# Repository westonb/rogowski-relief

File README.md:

# rogowski-relief
## An open source rogowski coil based current probe

This project is a rogowski coil based current probe designed to measure high frequency AC currents in tight spaces.
The sensing coil is optimized to be small enough to fit between the leads of a TO-220 transistor and can be slipped around the leads of many through hole power components for non-intrusive current measurements. 
The project consists of the rogowski coil and the integrator/amplifier which conditions the signal from the rogowski coil and provides an output voltage proportional to the current flowing in a conductor encircled by the rogowski coil. 

## Operation
The sensing coil is open ended, with the free end held in place by a captive O-ring.
The enables the coil to be placed around a wire without breaking the circuit.
The amplifier provides a 0.1V/A output through a SMA connector and is designed to drive a 1M oscilloscope input through a coaxial cable. 
The amplifier is powered through a USB-B connector and draws less than 2W. 

## Specifications 

### Typical Electrical Performance

- **Bandwidth**: 800 Hz - 25 MHz
- **Sensitivity**: 0.1 Volts/Amp
- **Max Current**: +/- 30 A
- **Noise**: 6 mA RMS
- **Slew Rate**: 1 A/ns 

### Coil
- **OD**: < 1.7mm
- **Length**: 70mm

## Project Status
The current probe meets the original design goals and is suitable for general purpose lab use.
The most recently fabricated version of the integrator had some issues with interference from wireless signals (WiFi and LTE).
The PCB files in the latest commit have layout changes to fit the circuitry under a metal shielding can, which should largely remedy the issue.
There are only minor electrical revisions in the updated version, but it remains untested.

## Project Files

LTSpice simulation files for the time domain and frequency domain as well as noise simulation of the system are in the [sim](sim/) directory.
PCB design files and schematics are in the [PCB](pcb/) directory.
STL files of for the rogowski coil, mechanical BOM, and build instructions are in the [mech](mech/) directory.
Schematic of the integrator provided below for convenience. 

## Operating Principles 

### Rogowski Coil

|  | 
|:--:| 
| *Rogowski Coil Drawing. Source: [Wikipedia](https://en.wikipedia.org/wiki/File:Rogowski_coil.png)* |

A rogowski coil is a toroidally wound air coil, consisting of many turns of wire wrapped around a coil form, with the start and end of the coil form joined together.
Each turn of the coil generates a voltage proportional to the change in the coupled magnetic field.
The sum of the voltage produced by all the turns is proportional to the change in the line integral of magnetic field around the path of the coil. 
As expressed by Ampere's law, the line integral of the magnetic field for any closed path is proportional to the current flowing in the enclosed area. 
Thus, the rogowski coil produces a voltage proportional to the change in current in a wire encircled by the coil with the output signal independent of the positioning of the wire. 
This allows for a flexible air-cored current sensor.
Unlike a current transformer, the rogowski coil generates a voltage proportional to the dI/dt and the signal must be integrated to produce an output proportional to current.
Additionally, as the dI/dt of a DC current is zero, the rogowski coil can not measure a DC current. 

|  | 
|:--:| 
| *Circuit Model of Rogowski Coil* |

The rogowski coil can be modeled as a mutual inductance representing the flux coupling between the encircled wire and the coil, and the physical inductance and capacitance of the coil.
The induced signal can be modeled as a current source equal to that of the current in the encircled wire that is parallel with the mutual inductance.
The inductance and capacitance of the coil limit the maximum bandwidth and are dependent on the geometry of the coil.
The winding diameter and pitch determine the characteristic impedance of the coil, which determines the ratio of inductance to capacitance.
The bandwidth of the rogowski coil is maximized when the coil is terminated with a resistance equal to the characteristic impedance.
The total values of inductance and capacitance are determined by the length of the coil, which is proportional to the number of turns.

### Integrator
This project uses an op-amp based integrator to process the signal from the rogowski coil.
As integrator gain increases at low frequencies, the noise of the integrator ultimately limits the achievable low frequency bandwidth and is one of the most important design criteria.

This design uses an non-inverting integrator, best described in the paper [High Performance Rogowski Current Transducers](https://gmw.com/wp-content/uploads/2019/01/ias_2000_pem.pdf), and a servo high-pass filter with a second op-amp, best described in [A new filter topology for analog high-pass filters](https://www.ti.com/lit/an/slyt299/slyt299.pdf) to roll off the low frequency gain.

|  | 
|:--:| 
| *Annotated schematic of Rogowski coil and integrator* |

The non-inverting integrator consists of a passive RC integrator for high frequency integration and an op-amp integrator for low frequencies.
The passive RC integrator is comprised of the termination resistor for the rogowski coil, which matches the characteristic impedance of the rogowski coil and is co-located with the rogowski coil.
This allows for the capacitance of the cable between the rogowski coil and the integrator, which would otherwise limit bandwidth, to be incorporated as part of the integrator capacitance.
The non-inverting integrator requires that the crossover frequencies of the passive RC integrator and the op-amp match, necessitating a trimmer resistor.

The servo high-pass filter reduces the gain of the integrator below the cutoff frequency instead of leveling off the gain.
This reduces the noise of the system and nulls the DC offset of the amplifier, which could otherwise limit the output signal range.

An additional op-amp is used as an output buffer to provide adjustable gain to normalize the output to a fixed V/A ratio, and provide high frequency peaking to compensate for losses in the rogowski coil.

The op-amp used for the integrator was chosen for its low noise and high bandwidth.
Changing the op-amp can drastically change the output noise.

### Power Supply
The integrator is powered through a USB-B connector.
An isolated DC/DC converter module is uses to provide bipolar outputs of +/-9V which is then regulated down to +/-6V with linear regulators.
The linear regulators reduce switching noise which could otherwise couple into the output.
The isolated DC/DC converters are a commodity component that provide a bipolar output with lower cost and complexity than could be achieved with a solution using discrete components.
Additionally, the isolated module prevents any return current from passing through the output cable, which can inject noise or cause a DC offset.

## Safety 
No safety guarantees or warranty is implied for this design.
However, some safety precautions were taken as the rogowski coil could come into contact with conductors that are at a high voltage.
A PCB trace fuse on both connections from the coil is included on the PCB layout in the hope that the traces will blow and isolate the coil if the coil arcs over.
Additionally, a gas discharge tube is included on the output to further protect a connected device if such an arc-over would occur.

No voltage rating of the rogowski coil is implied or tested
The recommended heat-shrink has a wall thickness of 8 mil and a dielectric strength of 2kV/mil.
The recommended magnetic wire is MW 35-C rated and as such has a minimum dielectric strength of 2340V.
Mechanical wear and high dv/dt signals both adversely impact the voltage rating.

## Demo
|  | 
|:--:| 
| *Probe step response. Reference (yellow) and probe output (orange)* |

|  | 
|:--:| 
| *Output Noise and FFT* |

|  | 
|:--:| 
| *Probe frequency response* |

|   | 
|:--:| 
| *Probing primary current (yellow) and output choke current (orange) of a SMPS* |

## Open Source
This work is licensed under a
[Creative Commons Attribution-ShareAlike 4.0 International License][cc-by-sa].

[![CC BY-SA 4.0][cc-by-sa-image]][cc-by-sa]

[cc-by-sa]: http://creativecommons.org/licenses/by-sa/4.0/
[cc-by-sa-image]: https://licensebuttons.net/l/by-sa/4.0/88x31.png
[cc-by-sa-shield]: https://img.shields.io/badge/License-CC%20BY--SA%204.0-lightgrey.svg

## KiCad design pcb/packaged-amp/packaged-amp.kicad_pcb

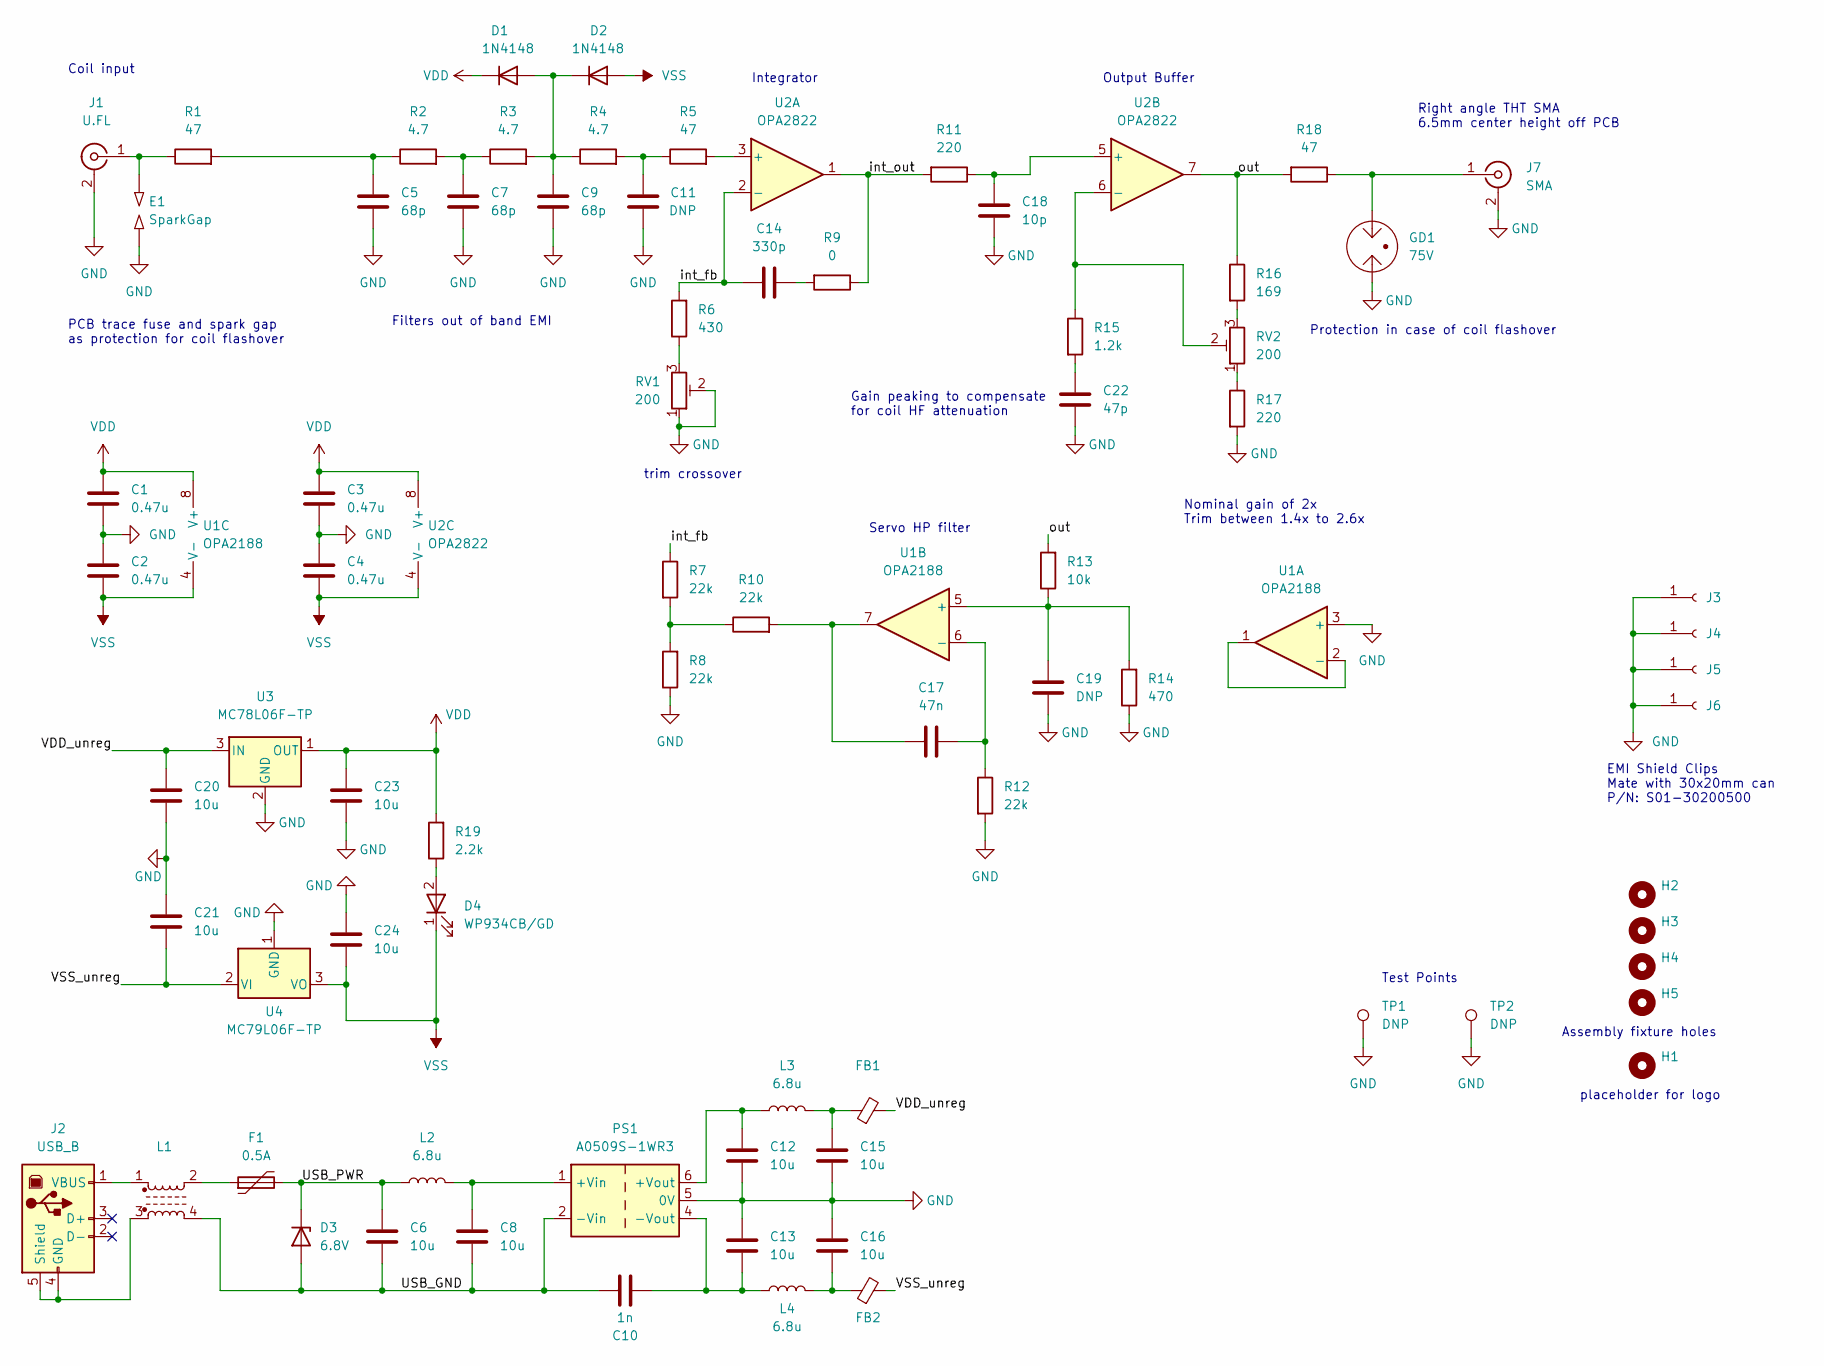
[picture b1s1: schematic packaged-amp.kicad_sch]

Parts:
C1, C2, C3, C4: 0.47u; C_0603_1608Metric; MPN CL10B474KA8NNNC; JLC_MPN C1623
C5, C7, C9: 68p; C_0603_1608Metric; MPN CL10C680JB8NNNC; JLC_MPN C28262
C6, C8, C12, C13, C15, C16, C20, C21, C23, C24: 10u; C_1206_3216Metric; MPN CL31A106KBHNNNE; JLC_MPN C13585
C10: 1n; C_1206_3216Metric; MPN 1206B102K202NT; JLC_MPN C9196
C11, C19: DNP; C_0603_1608Metric
C14: 330p; C_0603_1608Metric; MPN CL10C331JB8NNNC; JLC_MPN C1664
C17: 47n; C_1206_3216Metric; MPN GRM31M5C1H473JA01L; JLC_MPN C21812
C18: 10p; C_0603_1608Metric; MPN CL10C100JB8NNNC; JLC_MPN C1634
C22: 47p; C_0603_1608Metric; MPN CL10C470JB8NNNC; JLC_MPN C1671
D1, D2: 1N4148; D_SOD-323F; MPN 1N4148WS RRG; JLC_MPN C2128
D3: 6.8V; D_SMB; MPN P6SMB6.8CA/TR13; JLC_MPN C78395
D4: WP934CB/GD; LED-T1-RIGHT-ANGLE_4.6x4.4mm; MPN WP934CB/GD; JLC_MPN C2929607
E1: SparkGap; Spark_Gap
F1: 0.5A; Fuse_0603_1608Metric; MPN 0467.750NRHF; JLC_MPN C206991
FB1, FB2: FerriteBead_Small; L_0805_2012Metric; MPN 742792040; JLC_MPN C1015
GD1: 75V; GDT_1812; MPN 4532-075-LF; JLC_MPN C522627
H1: MountingHole; beefield_logo_small
H2, H3, H4, H5: MountingHole; JLC_TOOLING_HOLE
J1: U.FL; U.FL_Hirose_U.FL-R-SMT-1_Vertical; MPN U.FL-R-SMT-1(10); JLC_MPN C88373
J2: USB_B; USB_B_OST_USB-B1HSxx_Horizontal; MPN USB-B1HSB6; JLC_MPN C498173
J3, J4, J5, J6: Conn_01x01_Female; CLIP_ECT81800C036; MPN S1001-46R; JLC_MPN C5446941
J7: SMA; SMA_Molex_73251-2200_Horizontal; MPN RF2-49B-T-00-50-G-HDW; JLC_MPN C1509208
L1: DLW5BTM142SQ2L; L_CommonModeChoke_Murata_DLW5BTM; MPN DLW5BTM142SQ2L; JLC_MPN C91596
L2, L3, L4: 6.8u; L_1210_3225Metric; MPN NLCV32T-6R8M-EF; JLC_MPN C250230
PS1: A0509S-1WR3; Converter_DCDC_XP_POWER-IHxxxxS_THT; MPN A0509S-1WR3; JLC_MPN C131900
R1, R5: 47; R_0603_1608Metric; MPN RC0603FR-0747RL; JLC_MPN C23182
R2, R3, R4: 4.7; R_0603_1608Metric; MPN RC0603JR-074R7L; JLC_MPN C23164
R6: 430; R_0603_1608Metric; MPN RC0603FR-07430RL; JLC_MPN C23170
R7, R8, R10, R12: 22k; R_0603_1608Metric; MPN RMCF0603FG22K0; JLC_MPN C31850
R9: 0; R_0603_1608Metric; MPN ERJ-3GEY0R00V; JLC_MPN C21189
R11, R17: 220; R_0603_1608Metric; MPN RC0603FR-07220RL; JLC_MPN C22962
R13: 10k; R_0603_1608Metric; MPN RC0603FR-0710KL; JLC_MPN C25804
R14: 470; R_0603_1608Metric; MPN RC0603FR-07470RL; JLC_MPN C23179
R15: 1.2k; R_0603_1608Metric; MPN RC0603FR-071K2L; JLC_MPN C22765
R16: 169; R_0603_1608Metric; MPN RC0603FR-07169RL; JLC_MPN C22889
R18: 47; R_1206_3216Metric; JLC_MPN C17969
R19: 2.2k; R_0603_1608Metric; MPN RC0603FR-072K2L; JLC_MPN C4190
RV1, RV2: 200; Potentiometer_Bourns_3314G_Vertical; MPN 3314G-1-201E; JLC_MPN C52238
TP1, TP2: DNP; THM_MINI
U1: OPA2188; SOIC-8_3.9x4.9mm_P1.27mm; MPN OPA2188AIDR; JLC_MPN C17271
U2: OPA2822; SOIC-8_3.9x4.9mm_P1.27mm; MPN OPA2822U; JLC_MPN C2059808
U3: MC78L06F-TP; SOT-89-3; MPN MC78L06F-TP; JLC_MPN C81358
U4: MC79L06F-TP; SOT-89-3; MPN MC79L06F-TP; JLC_MPN C8619

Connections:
/USB_GND: C6.2, C8.2, C10.1, D3.2 (A), L1.4, PS1.2 (-Vin)
/USB_PWR: C6.1, D3.1 (K), F1.2, L2.1
/VDD_unreg: C20.1, FB1.2, U3.3 (IN)
/VSS_unreg: C21.2, FB2.2, U4.2 (VI)
/int_fb: C14.1, R6.2, R7.1, U2.2 (-)
/int_out: R9.1, R11.2, U2.1
/out: R13.2, R16.1, R18.2, U2.7
GND: C1.2, C2.1, C3.2, C4.1, C5.2, C7.2, C9.2, C11.1, C12.2, C13.1, C15.2, C16.1, C18.2, C19.1, C20.2, C21.1, C22.2, C23.2, C24.1, E1.1, GD1.2, J1.2 (Ext), J3.1, J4.1, J5.1, J6.1, J7.2 (Ext), PS1.5 (0V), R8.1, R12.2, R14.1, R17.2, RV1.1, RV1.2, TP1.1, TP2.1, U1.3 (+), U3.2 (GND), U4.1 (GND)
unnamed: C5.1, R1.2, R2.1
unnamed: C8.1, L2.2, PS1.1 (+Vin)
unnamed: C14.2, R9.2
unnamed: C17.1, R10.2, U1.7
unnamed: C17.2, R12.1, U1.6 (-)
unnamed: C19.2, R13.1, R14.2, U1.5 (+)
unnamed: D4.2 (A), R19.1
unnamed: E1.2, J1.1 (In), R1.1
unnamed: C15.1, FB1.1, L3.2
unnamed: C16.2, FB2.1, L4.2
unnamed: GD1.1, J7.1 (In), R18.1
unnamed: J2.1 (VBUS), L1.1
unnamed: J2.4 (GND), J2.5 (Shield), L1.3
unnamed: F1.1, L1.2
unnamed: C10.2, C13.2, L4.1, PS1.4 (-Vout)
unnamed: C12.1, L3.1, PS1.6 (+Vout)
unnamed: C7.1, R2.2, R3.1
unnamed: C9.1, D1.2 (A), D2.1 (K), R3.2, R4.1
unnamed: C11.2, R4.2, R5.1
unnamed: R6.1, RV1.3
unnamed: R7.2, R8.2, R10.1
unnamed: C18.1, R11.1, U2.5 (+)
unnamed: C22.1, R15.2
unnamed: R16.2, RV2.3
unnamed: R17.1, RV2.1
unnamed: U1.1, U1.2 (-)
unnamed: R5.2, U2.3 (+)
unnamed: R15.1, RV2.2, U2.6 (-)
VDD: C1.1, C3.1, C23.1, D1.1 (K), R19.2, U1.8 (V+), U2.8 (V+), U3.1 (OUT)
VSS: C2.2, C4.2, C24.2, D2.2 (A), D4.1 (K), U1.4 (V-), U2.4 (V-), U4.3 (VO)

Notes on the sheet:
Coil input
Gain peaking to compensate for coil HF attenuation
Servo HP filter
Integrator
PCB trace fuse and spark gap as protection for coil flashover
Test Points
Output Buffer
Protection in case of coil flashover
Right angle THT SMA 6.5mm center height off PCB
Filters out of band EMI
Assembly fixture holes
placeholder for logo
EMI Shield Clips Mate with 30x20mm can P/N: S01-30200500
Nominal gain of 2x Trim between 1.4x to 2.6x
trim crossover

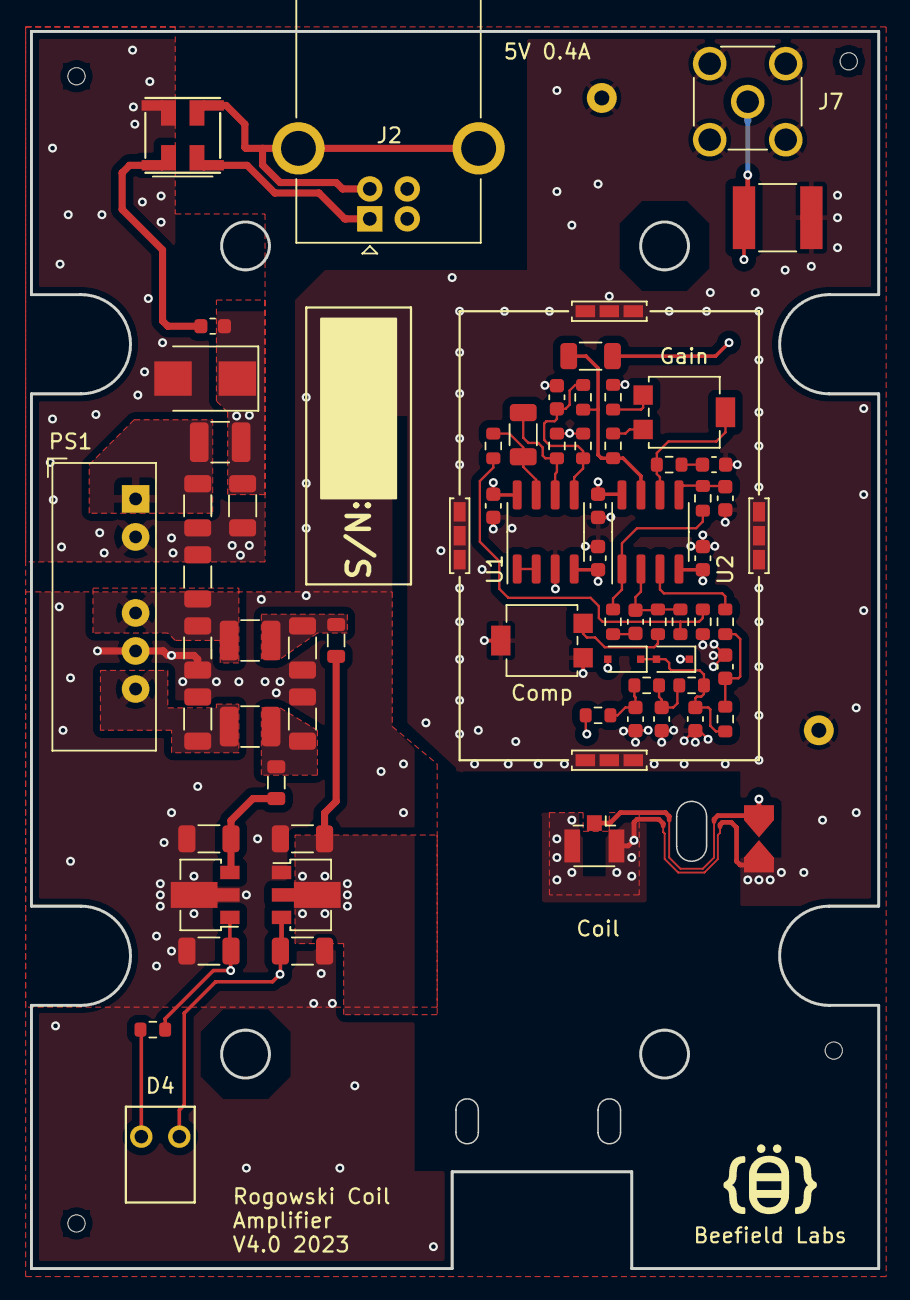
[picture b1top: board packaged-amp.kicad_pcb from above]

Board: 4 copper layers, 56.6 x 82.7 mm, 77 parts (0 on the bottom side), 38 nets.

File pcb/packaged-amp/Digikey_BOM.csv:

"Ref","Qty","Value","Footprint","Description","MPN"
"C1, C2, C3, C4, ","4","0.47u","Capacitor_SMD:C_0603_1608Metric","Unpolarized capacitor","CL10B474KA8NNNC"
"C5, C7, C9, ","3","68p","Capacitor_SMD:C_0603_1608Metric","Unpolarized capacitor","CL10C680JB8NNNC"
"C6, C8, C12, C13, C15, C16, C20, C21, C23, C24, ","10","10u","Capacitor_SMD:C_1206_3216Metric","Unpolarized capacitor","CL31A106KBHNNNE"
"C10, ","1","1n","Capacitor_SMD:C_1206_3216Metric","Unpolarized capacitor","1206B102K202NT"
"C11, C19, ","2","DNP","Capacitor_SMD:C_0603_1608Metric","Unpolarized capacitor",""
"C14, ","1","330p","Capacitor_SMD:C_0603_1608Metric","Unpolarized capacitor","CL10C331JB8NNNC"
"C17, ","1","47n","Capacitor_SMD:C_1206_3216Metric","Unpolarized capacitor","GRM31M5C1H473JA01L"
"C18, ","1","10p","Capacitor_SMD:C_0603_1608Metric","Unpolarized capacitor","CL10C100JB8NNNC"
"C22, ","1","47p","Capacitor_SMD:C_0603_1608Metric","Unpolarized capacitor","CL10C470JB8NNNC"
"D1, D2, ","2","1N4148","Diode_SMD:D_SOD-323F","Diode","1N4148WS RRG"
"D3, ","1","6.8V","Diode_SMD:D_SMB","Zener diode","P6SMB6.8CA/TR13"
"D4, ","1","WP934CB/GD","wbraun_smd:LED-T1-RIGHT-ANGLE_4.6x4.4mm","Light emitting diode","WP934CB/GD"
"E1, ","1","SparkGap","wbraun_smd:Spark_Gap","Spark gap",""
"F1, ","1","0.5A","Fuse:Fuse_0603_1608Metric","Resettable fuse, polymeric positive temperature coefficient","0467.750NRHF"
"FB1, FB2, ","2","FerriteBead_Small","Inductor_SMD:L_0805_2012Metric","Ferrite bead, small symbol","742792040"
"GD1, ","1","75V","wbraun_smd:GDT_1812","Gas Discharge Tube with 2 Pins","4532-075-LF"
"H1, ","1","MountingHole","wbraun_smd:beefield_logo_small","Mounting Hole without connection",""
"H2, H3, H4, H5, ","4","MountingHole","wbraun_smd:JLC_TOOLING_HOLE","Mounting Hole without connection",""
"J1, ","1","U.FL","Connector_Coaxial:U.FL_Hirose_U.FL-R-SMT-1_Vertical","coaxial connector (BNC, SMA, SMB, SMC, Cinch/RCA, LEMO, ...)","U.FL-R-SMT-1(10)"
"J2, ","1","USB_B","wbraun_smd:USB_B_OST_USB-B1HSxx_Horizontal","USB Type B connector","USB-B1HSB6"
"J3, J4, J5, J6, ","4","Conn_01x01_Female","wbraun_smd:CLIP_ECT81800C036","Generic connector, single row, 01x01, script generated (kicad-library-utils/schlib/autogen/connector/)","S1001-46R"
"J7, ","1","SMA","wbraun_smd:SMA_Molex_73251-2200_Horizontal","coaxial connector (BNC, SMA, SMB, SMC, Cinch/RCA, LEMO, ...)","RF2-49B-T-00-50-G-HDW"
"L1, ","1","DLW5BTM142SQ2L","wbraun_smd:L_CommonModeChoke_Murata_DLW5BTM","Coupled inductor with ferrite core","DLW5BTM142SQ2L"
"L2, L3, L4, ","3","6.8u","Inductor_SMD:L_1210_3225Metric","Inductor","NLCV32T-6R8M-EF"
"PS1, ","1","A0509S-1WR3","Converter_DCDC:Converter_DCDC_XP_POWER-IHxxxxS_THT","XP Power 2W, 1000 VDC Isolated DC/DC Converter Module, Dual Output Voltage ±3.3V, ±200mA, 5V Input Voltage, SIP","A0509S-1WR3"
"R1, R5, ","2","47","Resistor_SMD:R_0603_1608Metric","Resistor","RC0603FR-0747RL"
"R2, R3, R4, ","3","4.7","Resistor_SMD:R_0603_1608Metric","Resistor","RC0603JR-074R7L"
"R6, ","1","430","Resistor_SMD:R_0603_1608Metric","Resistor","RC0603FR-07430RL"
"R7, R8, R10, R12, ","4","22k","Resistor_SMD:R_0603_1608Metric","Resistor","RMCF0603FG22K0"
"R9, ","1","0","Resistor_SMD:R_0603_1608Metric","Resistor","ERJ-3GEY0R00V"
"R11, R17, ","2","220","Resistor_SMD:R_0603_1608Metric","Resistor","RC0603FR-07220RL"
"R13, ","1","10k","Resistor_SMD:R_0603_1608Metric","Resistor","RC0603FR-0710KL"
"R14, ","1","470","Resistor_SMD:R_0603_1608Metric","Resistor","RC0603FR-07470RL"
"R15, ","1","1.2k","Resistor_SMD:R_0603_1608Metric","Resistor","RC0603FR-071K2L"
"R16, ","1","169","Resistor_SMD:R_0603_1608Metric","Resistor","RC0603FR-07169RL"
"R18, ","1","47","Resistor_SMD:R_1206_3216Metric","Resistor",""
"R19, ","1","2.2k","Resistor_SMD:R_0603_1608Metric","Resistor","RC0603FR-072K2L"
"RV1, RV2, ","2","200","Potentiometer_SMD:Potentiometer_Bourns_3314G_Vertical","Trim-potentiometer","3314G-1-201E"
"TP1, TP2, ","2","DNP","wbraun_smd:THM_MINI","test point",""
"U1, ","1","OPA2188","Package_SO:SOIC-8_3.9x4.9mm_P1.27mm","Dual SoundPlus High Performance, Bipolar-Input Audio Operational Amplifiers, SOIC-8/MSOP-8","OPA2188AIDR"
"U2, ","1","OPA2822","Package_SO:SOIC-8_3.9x4.9mm_P1.27mm","Dual SoundPlus High Performance, Bipolar-Input Audio Operational Amplifiers, SOIC-8/MSOP-8","OPA2822U"
"U3, ","1","MC78L06F-TP","Package_TO_SOT_SMD:SOT-89-3","Positive 100mA 30V Linear Regulator, Fixed Output 6V, SOT-89","MC78L06F-TP"
"U4, ","1","MC79L06F-TP","Package_TO_SOT_SMD:SOT-89-3","Negative 100mA -30V Linear Regulator, Fixed Output -5V, SOT-89","MC79L06F-TP"

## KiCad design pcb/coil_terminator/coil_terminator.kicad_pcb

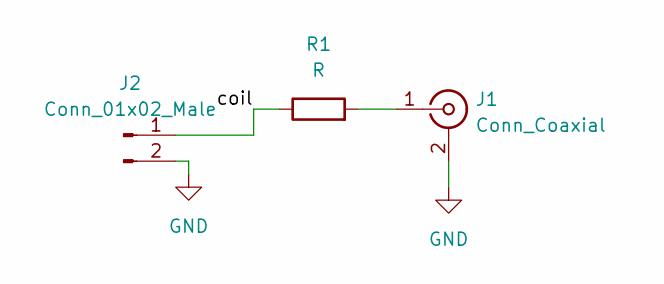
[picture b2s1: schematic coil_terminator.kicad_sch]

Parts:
J1: Conn_Coaxial; U.FL_Hirose_U.FL-R-SMT-1_Vertical
J2: Conn_01x02_Male; PinHeader_1x02_P1.27mm_Vertical
R1: R; R_1206_3216Metric_Pad1.30x1.75mm_HandSolder

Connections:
/coil: J2.1, R1.1
GND: J1.2 (Ext), J2.2
unnamed: J1.1 (In), R1.2

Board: 2 copper layers, 3 parts (0 on the bottom side), 3 nets, no tracks yet.

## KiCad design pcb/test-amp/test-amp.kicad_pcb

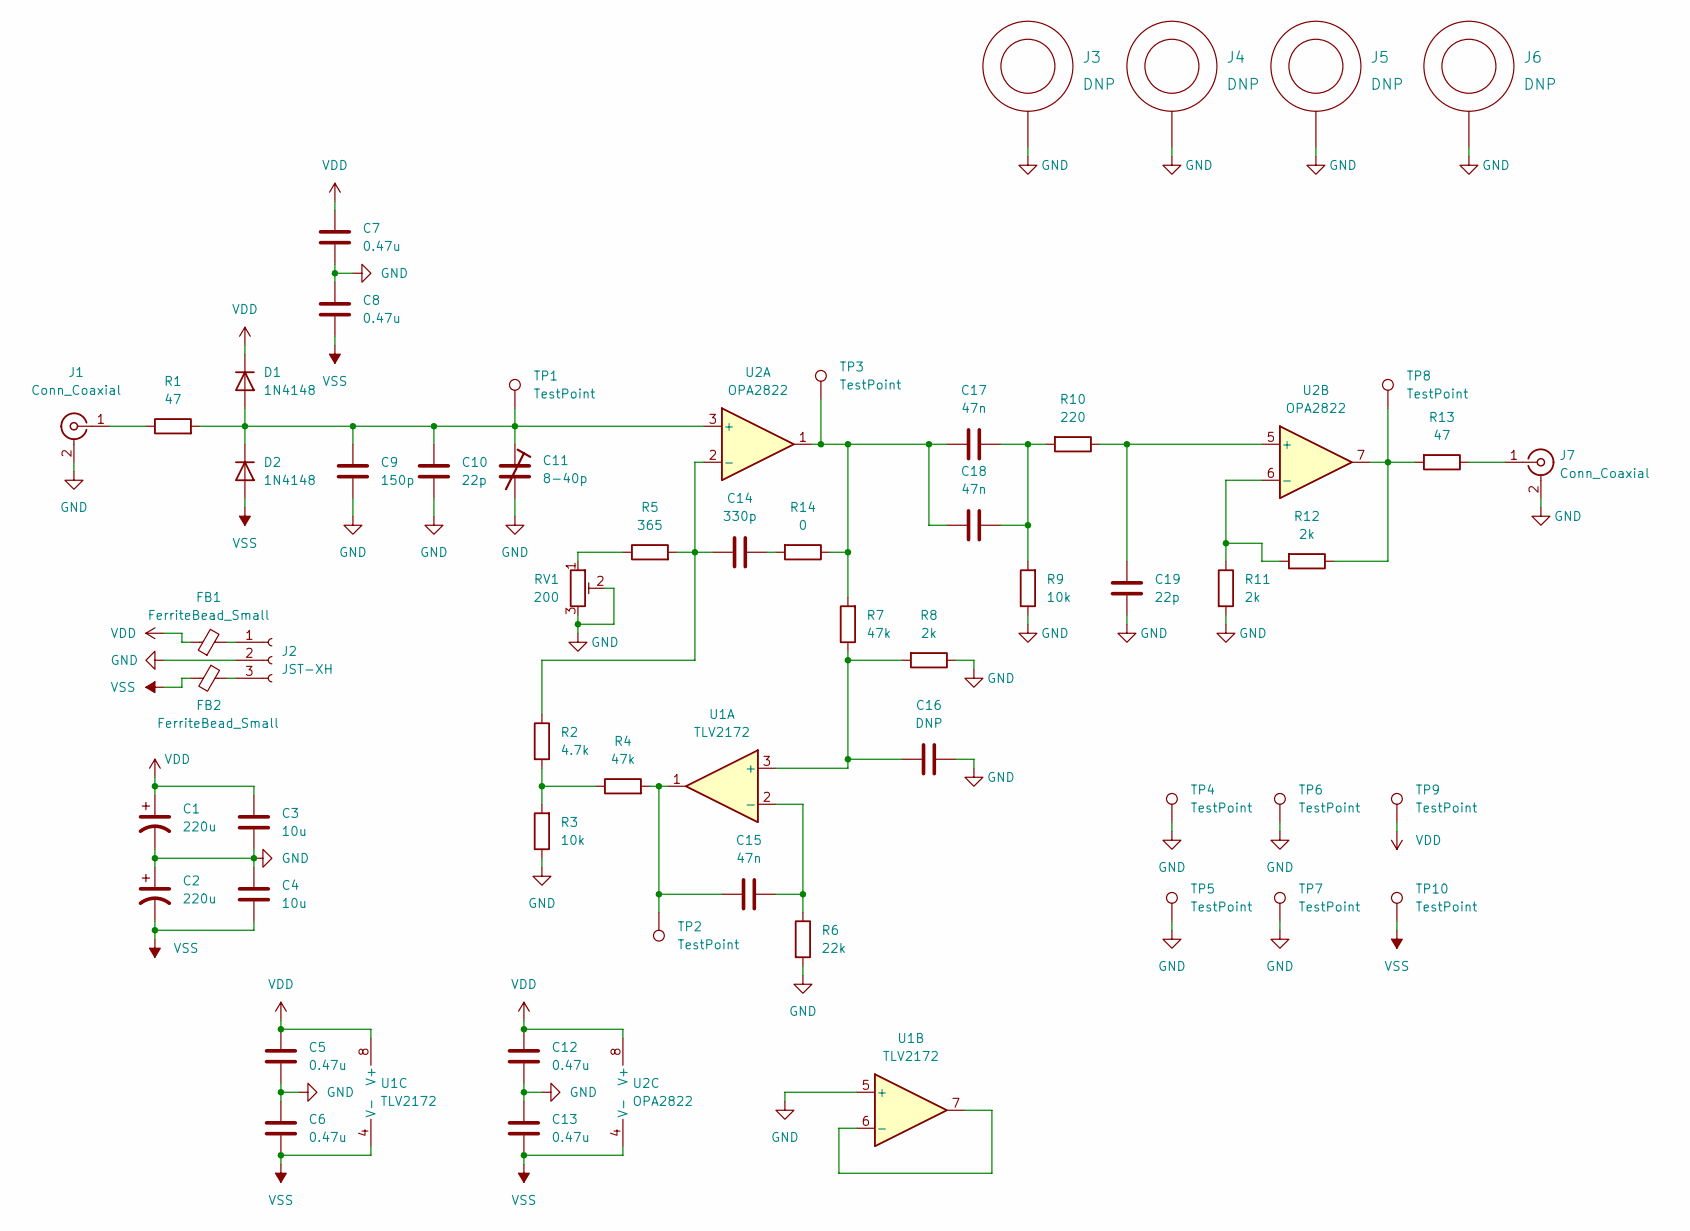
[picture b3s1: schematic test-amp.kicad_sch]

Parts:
C1, C2: 220u; CP_Radial_D8.0mm_P3.50mm; MPN 227KXM025M
C3, C4: 10u; C_1206_3216Metric
C5, C6, C7, C8, C12, C13: 0.47u; C_0603_1608Metric
C9: 150p; C_0603_1608Metric
C10, C19: 22p; C_0603_1608Metric
C11: 8-40p; C_Trimmer_Voltronics_JZ
C14: 330p; C_0603_1608Metric
C15, C17, C18: 47n; C_0805_2012Metric; MPN C3216C0G1H473J115AA
C16: DNP; C_0603_1608Metric
D1, D2: 1N4148; D_SOD-323F; MPN 1N4148WS RRG
FB1, FB2: FerriteBead_Small; L_0805_2012Metric
J1, J7: Conn_Coaxial; SMA-Edge-China
J2: JST-XH; JST_XH_B3B-XH-A_1x03_P2.50mm_Vertical
J3, J4, J5, J6: DNP; M3-tight-fit-socket-head
R1, R13: 47; R_1206_3216Metric
R2: 4.7k; R_0603_1608Metric
R3, R9: 10k; R_0603_1608Metric
R4, R7: 47k; R_0603_1608Metric
R5: 365; R_0603_1608Metric
R6: 22k; R_0603_1608Metric
R8, R11, R12: 2k; R_0603_1608Metric
R10: 220; R_0603_1608Metric
R14: 0; R_0603_1608Metric
RV1: 200; TRIMMER_PVG3A
TP1, TP2, TP3, TP4, TP5, TP6, TP7, TP8, TP9, TP10: TestPoint; THM_COMPACT
U1: TLV2172; SOIC-8_3.9x4.9mm_P1.27mm
U2: OPA2822; SOIC-8_3.9x4.9mm_P1.27mm

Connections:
GND: C1.2, C2.1, C3.2, C4.1, C5.2, C6.1, C7.2, C8.1, C9.2, C10.2, C11.2, C12.2, C13.1, C16.2, C19.2, J1.2 (Ext), J2.2, J3.1, J4.1, J5.1, J6.1, J7.2 (Ext), R3.1, R6.2, R8.1, R9.1, R11.2, RV1.2, RV1.3, TP4.1, TP5.1, TP6.1, TP7.1, U1.5 (+)
unnamed: C9.1, C10.1, C11.1, D1.2 (A), D2.1 (K), R1.2, TP1.1, U2.3 (+)
unnamed: C14.1, R2.1, R5.2, U2.2 (-)
unnamed: C14.2, R14.2
unnamed: C15.1, R4.2, TP2.1, U1.1
unnamed: C15.2, R6.1, U1.2 (-)
unnamed: C16.1, R7.1, R8.2, U1.3 (+)
unnamed: C17.1, C18.1, R7.2, R14.1, TP3.1, U2.1
unnamed: C17.2, C18.2, R9.2, R10.2
unnamed: C19.1, R10.1, U2.5 (+)
unnamed: FB1.2, J2.1
unnamed: FB2.1, J2.3
unnamed: J1.1 (In), R1.1
unnamed: J7.1 (In), R13.1
unnamed: R2.2, R3.2, R4.1
unnamed: R5.1, RV1.1
unnamed: R11.1, R12.2, U2.6 (-)
unnamed: R12.1, R13.2, TP8.1, U2.7
unnamed: U1.6 (-), U1.7
VDD: C1.1, C3.1, C5.1, C7.1, C12.1, D1.1 (K), FB1.1, TP9.1, U1.8 (V+), U2.8 (V+)
VSS: C2.2, C4.2, C6.2, C8.2, C13.2, D2.2 (A), FB2.2, TP10.1, U1.4 (V-), U2.4 (V-)

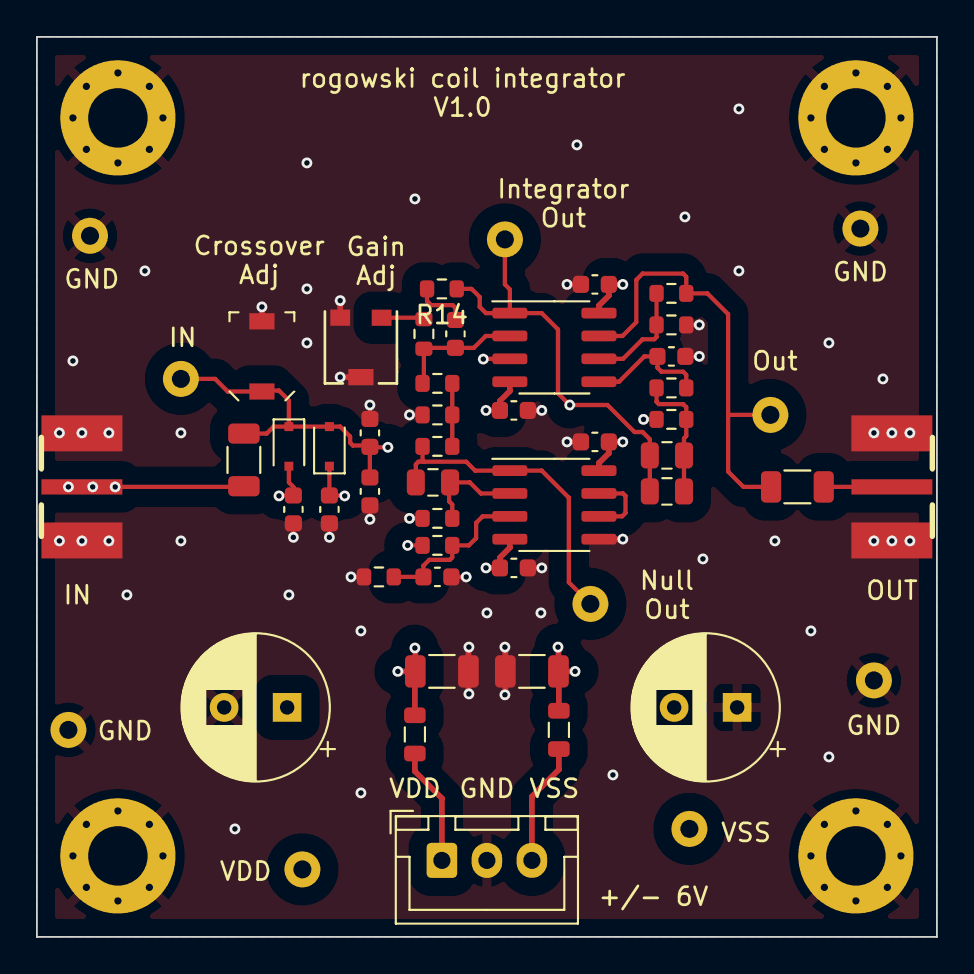
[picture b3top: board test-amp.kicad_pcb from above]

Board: 4 copper layers, 50.0 x 50.0 mm, 57 parts (0 on the bottom side), 21 nets.

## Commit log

2022-10-09 inial project files
2022-10-10 finished design of packaged amp
2022-10-15 design sent to fab
2022-11-11 next design revision
2022-11-13 design revision
2022-11-13 updated panels
2022-11-14 pcb sent to production
2022-12-16 added models for compensating coil loss
2023-01-08 next revision
2023-06-20 first public release
